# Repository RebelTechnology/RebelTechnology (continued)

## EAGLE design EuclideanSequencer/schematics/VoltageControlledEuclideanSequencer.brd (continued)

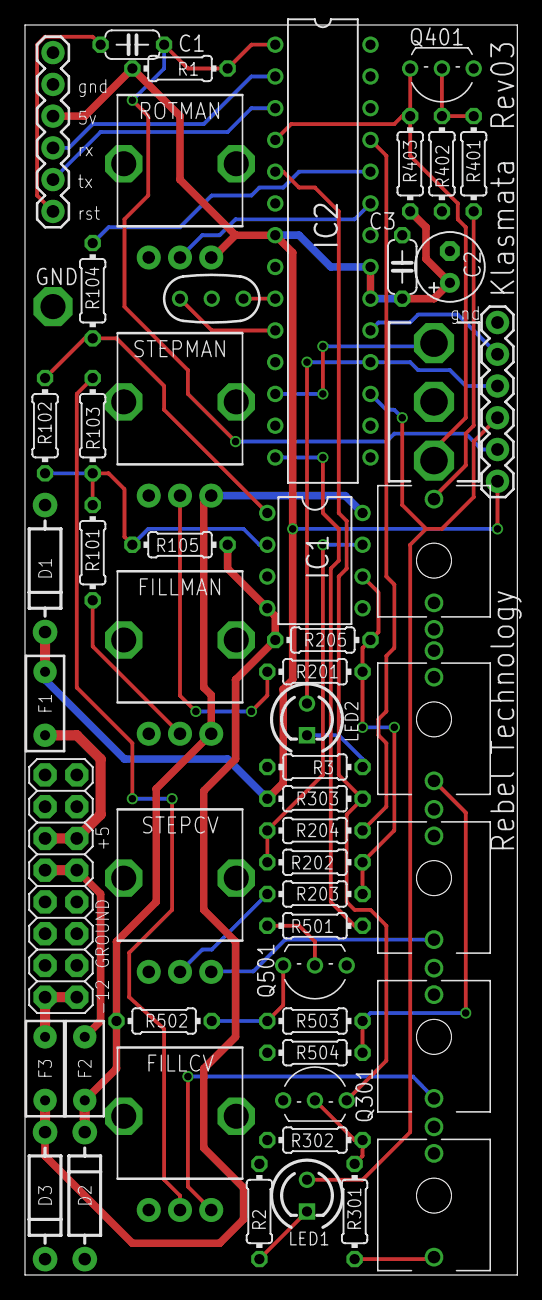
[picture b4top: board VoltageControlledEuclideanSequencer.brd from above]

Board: 2 copper layers, 39.4 x 100.0 mm, 57 parts (0 on the bottom side), 42 nets.

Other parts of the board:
U$1: RT-LOGO-REBEL-BL
U$3: RT-LOGO-TECH-BL

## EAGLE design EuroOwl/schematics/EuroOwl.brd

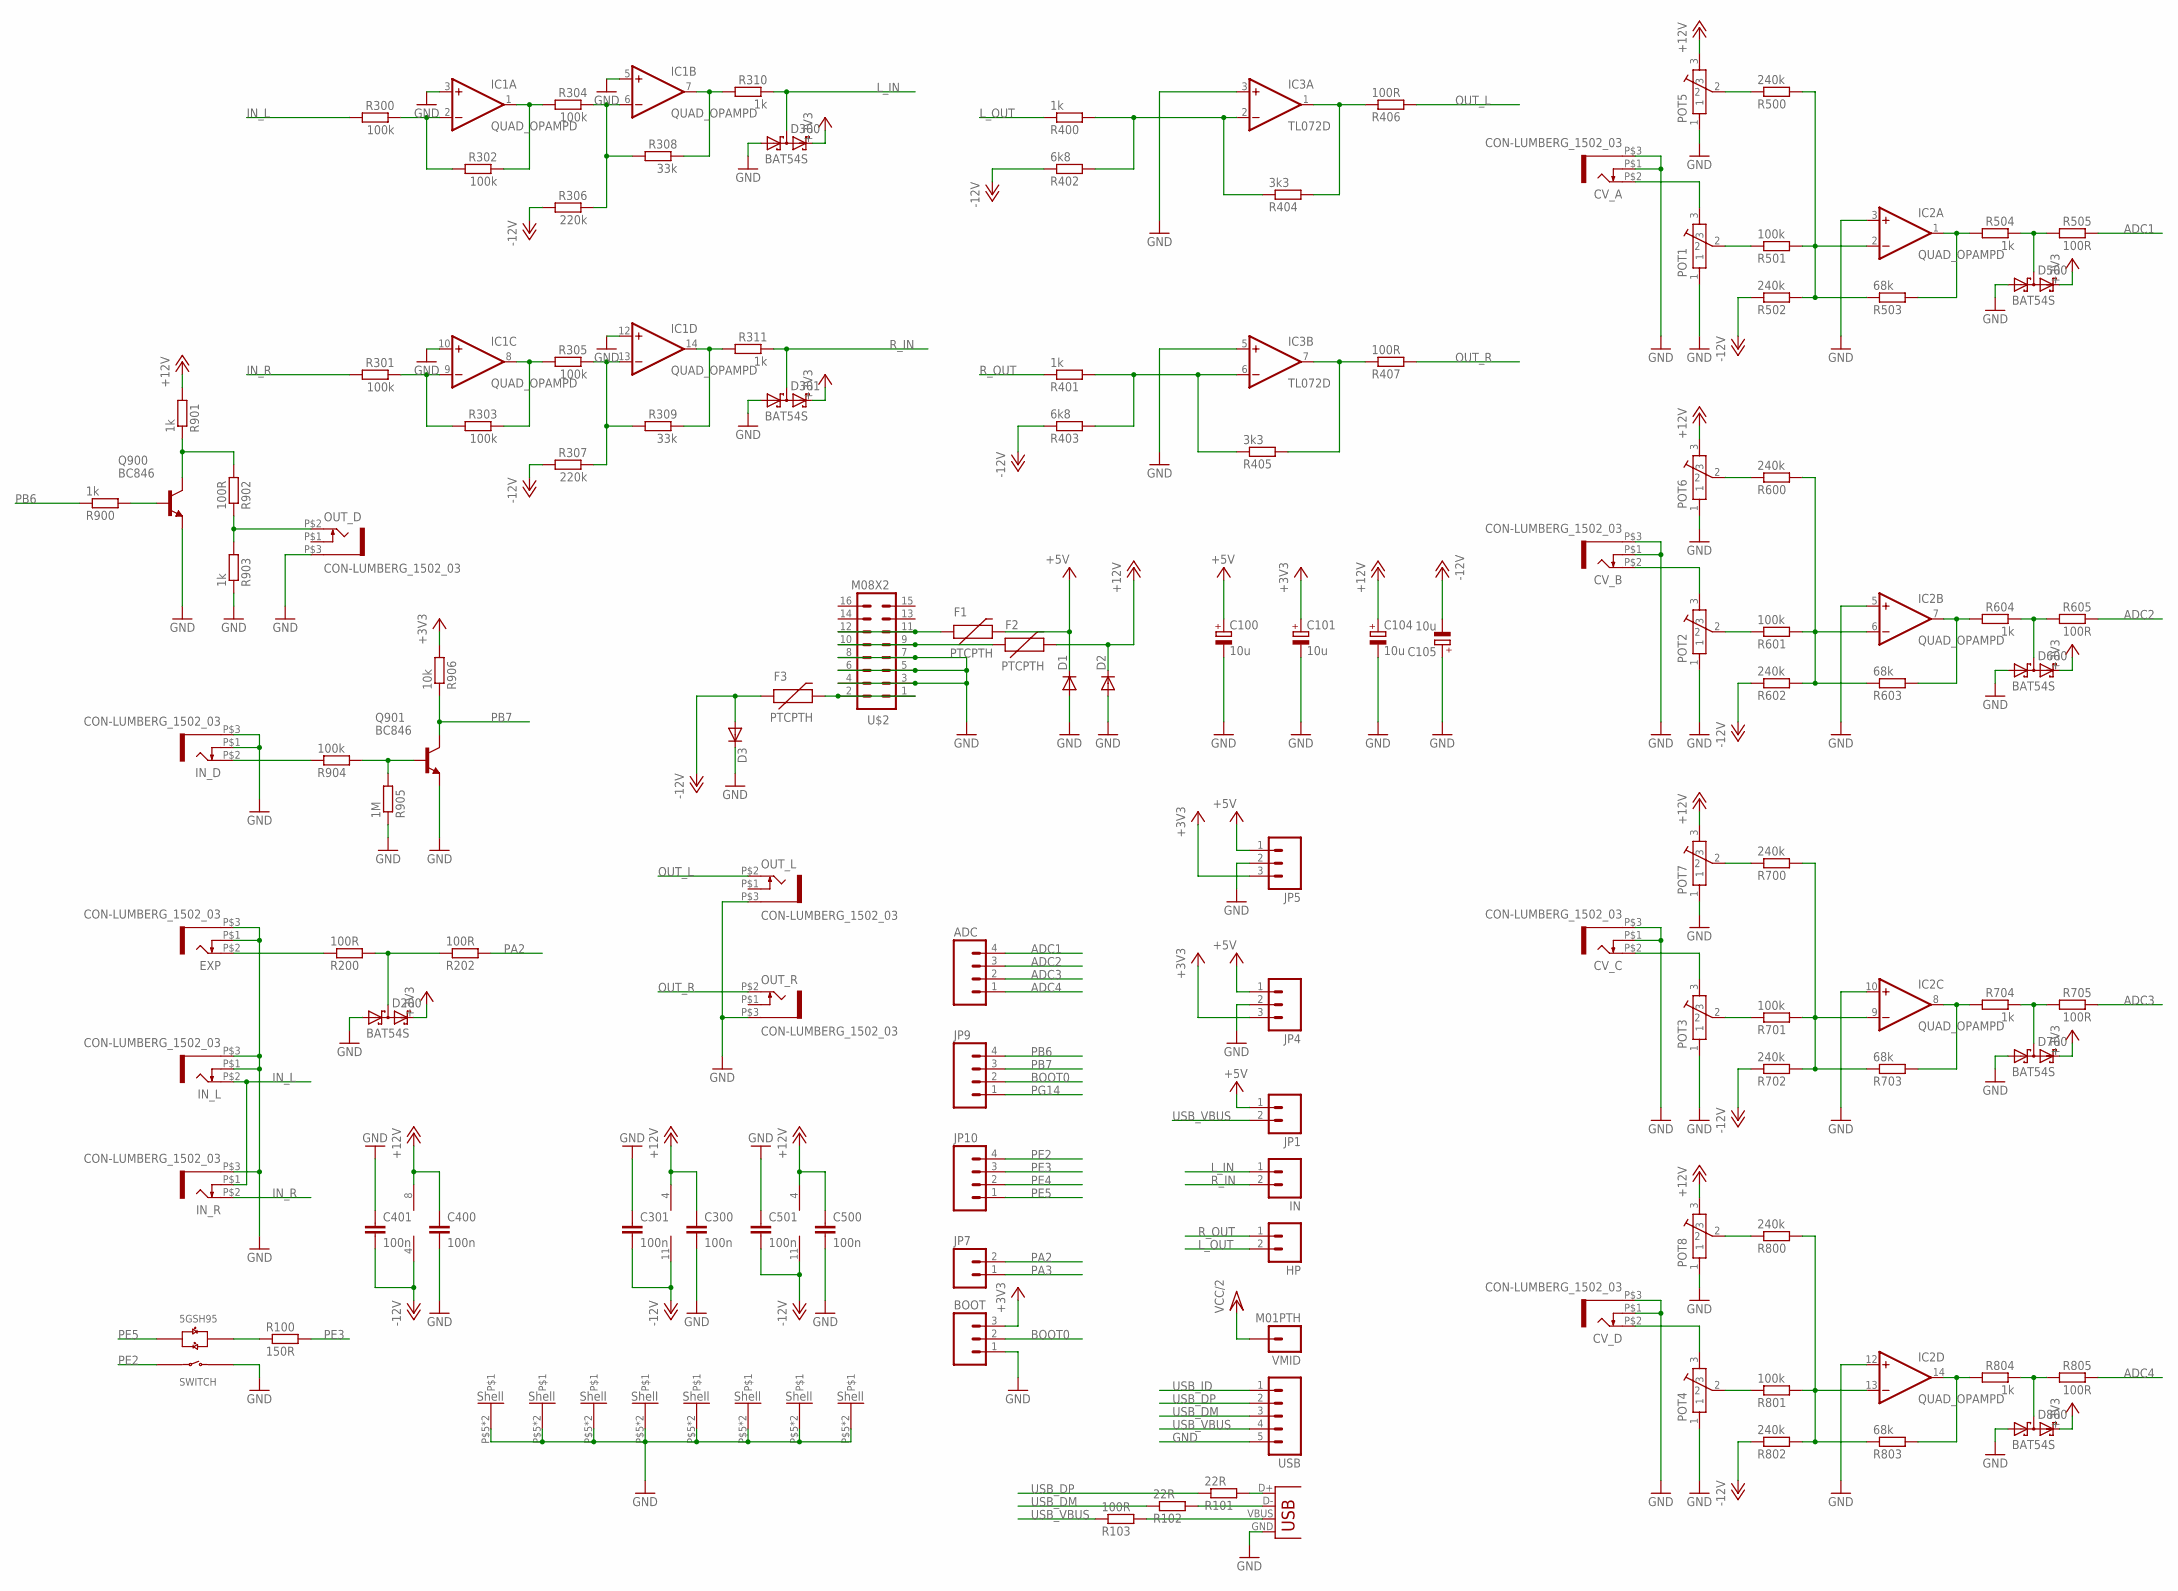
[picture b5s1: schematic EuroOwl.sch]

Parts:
ADC: M04PTH; 1X04
BOOT: M03PTH; 1X03
C100, C101, C104, C105: 10u; PANASONIC_A
C300, C301, C400, C401, C500, C501: 100n; C0603
CV_A: CON-LUMBERG_1502_03
CV_B: CON-LUMBERG_1502_03
CV_C: CON-LUMBERG_1502_03
CV_D: CON-LUMBERG_1502_03
D1, D2, D3: DIODE1N4001; DIODE-1N4001
D200, D300, D301, D500, D600, D700, D800: BAT54S; SOT23
EXP: CON-LUMBERG_1502_03
F1, F2, F3: PTCPTH; PTC
HP: M02PTH; 1X02
IC1, IC2: QUAD_OPAMPD; SO14
IC3: TL072D; SO08
IN: M02PTH; 1X02
IN_D: CON-LUMBERG_1502_03
IN_L: CON-LUMBERG_1502_03
IN_R: CON-LUMBERG_1502_03
JP1, JP7: M02PTH; 1X02
JP4, JP5: M03PTH; 1X03
JP9, JP10: M04PTH; 1X04
OUT_D: CON-LUMBERG_1502_03
OUT_L: CON-LUMBERG_1502_03
OUT_R: CON-LUMBERG_1502_03
POT1, POT2, POT3, POT4, POT5, POT6, POT7, POT8: POT-ALPS-RK09L1140
Q900, Q901: BC846; SOT23
R100: 150R; 0603
R101, R102: 22R; 0603
R103, R200, R202, R406, R407, R505, R605, R705, R805, R902: 100R; 0603
R300, R301, R302, R303, R304, R305, R501, R601, R701, R801, R904: 100k; 0603
R306, R307: 220k; 0603
R308, R309: 33k; 0603
R310, R311, R400, R401, R504, R604, R704, R804, R900, R901, R903: 1k; 0603
R402, R403: 6k8; 0603
R404, R405: 3k3; 0603
R500, R502, R600, R602, R700, R702, R800, R802: 240k; 0603
R503, R603, R703, R803: 68k; 0603
R905: 1M; 0603
R906: 10k; 0603
U$1: 5GTH9
U$2: M08X2; 2X8
USB: M05PTH; 1X05
VMID: M01PTH; 1X01
X1: USBPTH-VERTICAL; USB-B-PTH-VERTICAL

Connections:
+3V3: BOOT.3, C101.+, D200.2 (C2), D300.2 (C2), D301.2 (C2), D500.2 (C2), D600.2 (C2), D700.2 (C2), D800.2 (C2), JP4.3, JP5.3, R906.2
+5V: C100.+, D1.C, F1.P$2 (2), JP1.1, JP4.1, JP5.1
+12V: C104.+, C300.1, C400.1, C500.1, D2.C, F2.P$2 (2), IC1.4 (V+), IC2.4 (V+), IC3.8 (V+), POT5.3, POT6.3, POT7.3, POT8.3, R901.2
-12V: C105.-, C301.2, C401.2, C501.2, D3.A, F3.P$1 (1), IC1.11 (V-), IC2.11 (V-), IC3.4 (V-), R306.2, R307.2, R402.1, R403.1, R502.1, R602.1, R702.1, R802.1
ADC1: ADC.4, R505.1
ADC2: ADC.3, R605.1
ADC3: ADC.2, R705.1
ADC4: ADC.1, R805.1
BOOT0: BOOT.2, JP9.2
GND: BOOT.1, C100.-, C101.-, C104.-, C105.+, C300.2, C301.1, C400.2, C401.1, C500.2, C501.1, CV_A.P$1 (4), CV_A.P$3 (5), CV_B.P$1 (4), CV_B.P$3 (5), CV_C.P$1 (4), CV_C.P$3 (5), CV_D.P$1 (4), CV_D.P$3 (5), D1.A, D2.A, D3.C, D200.1 (A1), D300.1 (A1), D301.1 (A1), D500.1 (A1), D600.1 (A1), D700.1 (A1), D800.1 (A1), EXP.P$1 (4), EXP.P$3 (5), IC1.3 (+IN), IC1.5 (+IN), IC1.10 (+IN), IC1.12 (+IN), IC2.3 (+IN), IC2.5 (+IN), IC2.10 (+IN), IC2.12 (+IN), IC3.3 (+IN), IC3.5 (+IN), IN_D.P$1 (4), IN_D.P$3 (5), IN_L.P$1 (4), IN_L.P$3 (5), IN_R.P$3 (5), JP4.2, JP5.2, OUT_D.P$3 (5), OUT_L.P$3 (5), OUT_R.P$3 (5), POT1.1, POT1.P$5, POT1.P$6, POT2.1, POT2.P$5, POT2.P$6, POT3.1, POT3.P$5, POT3.P$6, POT4.1, POT4.P$5, POT4.P$6, POT5.1, POT5.P$5, POT5.P$6, POT6.1, POT6.P$5, POT6.P$6, POT7.1, POT7.P$5, POT7.P$6, POT8.1, POT8.P$5, POT8.P$6, Q900.2 (E), Q901.2 (E), R903.1, R905.1, U$1.1 (SWITCH_B), U$2.3, U$2.4, U$2.5, U$2.6, U$2.7, U$2.8, USB.5, X1.GND
IN_L: IN_L.P$2 (3), IN_R.P$1 (4), R300.2
IN_R: IN_R.P$2 (3), R301.2
L_IN: D300.3 (C1A2), IN.1, R310.1
L_OUT: HP.2, R400.1
unnamed: IC1.1 (OUT), R302.1, R304.2
unnamed: CV_A.P$2 (3), POT1.3
unnamed: POT1.2, R501.1
unnamed: IC1.8 (OUT), R303.1, R305.2
unnamed: IC1.9 (-IN), R301.1, R303.2
unnamed: F3.P$2 (2), U$2.1, U$2.2
unnamed: IC1.13 (-IN), R305.1, R307.1, R309.2
unnamed: IC1.2 (-IN), R300.1, R302.2
unnamed: R100.1, U$1.+3 (LED_R+)
unnamed: D200.3 (C1A2), R200.2, R202.1
unnamed: IC2.2 (-IN), R500.2, R501.2, R502.2, R503.1
unnamed: POT5.2, R500.1
unnamed: D500.3 (C1A2), R504.1, R505.2
unnamed: IC2.1 (OUT), R503.2, R504.2
unnamed: CV_B.P$2 (3), POT2.3
unnamed: POT2.2, R601.1
unnamed: IC2.6 (-IN), R600.2, R601.2, R602.2, R603.1
unnamed: POT6.2, R600.1
unnamed: IC2.7 (OUT), R603.2, R604.2
unnamed: D600.3 (C1A2), R604.1, R605.2
unnamed: CV_C.P$2 (3), POT3.3
unnamed: POT3.2, R701.1
unnamed: IC2.9 (-IN), R700.2, R701.2, R702.2, R703.1
unnamed: POT7.2, R700.1
unnamed: IC2.8 (OUT), R703.2, R704.2
unnamed: D700.3 (C1A2), R704.1, R705.2
unnamed: CV_D.P$2 (3), POT4.3
unnamed: POT4.2, R801.1
unnamed: IC1.6 (-IN), R304.1, R306.1, R308.2
unnamed: IC2.13 (-IN), R800.2, R801.2, R802.2, R803.1
unnamed: POT8.2, R800.1
unnamed: IC2.14 (OUT), R803.2, R804.2
unnamed: D800.3 (C1A2), R804.1, R805.2
unnamed: Q901.1 (B), R904.2, R905.2
unnamed: EXP.P$2 (3), R200.1
unnamed: IC3.1 (OUT), R404.2, R406.1
unnamed: IC3.7 (OUT), R405.2, R407.1
unnamed: IC3.2 (-IN), R400.2, R402.2, R404.1
unnamed: IC3.6 (-IN), R401.2, R403.2, R405.1
unnamed: F1.P$1 (1), U$2.11, U$2.12
unnamed: F2.P$1 (1), U$2.9, U$2.10
unnamed: IN_D.P$2 (3), R904.1
unnamed: Q900.3 (C), R901.1, R902.2
unnamed: OUT_D.P$2 (3), R902.1, R903.2
unnamed: Q900.1 (B), R900.2
unnamed: R101.2, X1.D+
unnamed: R102.2, X1.D-
unnamed: IC1.14 (OUT), R309.1, R311.2
unnamed: R103.2, X1.VBUS
unnamed: IC1.7 (OUT), R308.1, R310.2
OUT_L: OUT_L.P$2 (3), R406.2
OUT_R: OUT_R.P$2 (3), R407.2
PA2: JP7.2, R202.2
PA3: JP7.1
PB6: JP9.4, R900.1
PB7: JP9.3, Q901.3 (C), R906.1
PE2: JP10.4, U$1.4 (SWITCH_A)
PE3: JP10.3, R100.2
PE4: JP10.2
PE5: JP10.1, U$1.-2 (LED_G+)
PG14: JP9.1
R_IN: D301.3 (C1A2), IN.2, R311.1
R_OUT: HP.1, R401.1
USB_DM: R102.1, USB.3
USB_DP: R101.1, USB.2
USB_ID: USB.1
USB_VBUS: JP1.2, R103.1, USB.4
VCC/2: VMID.1

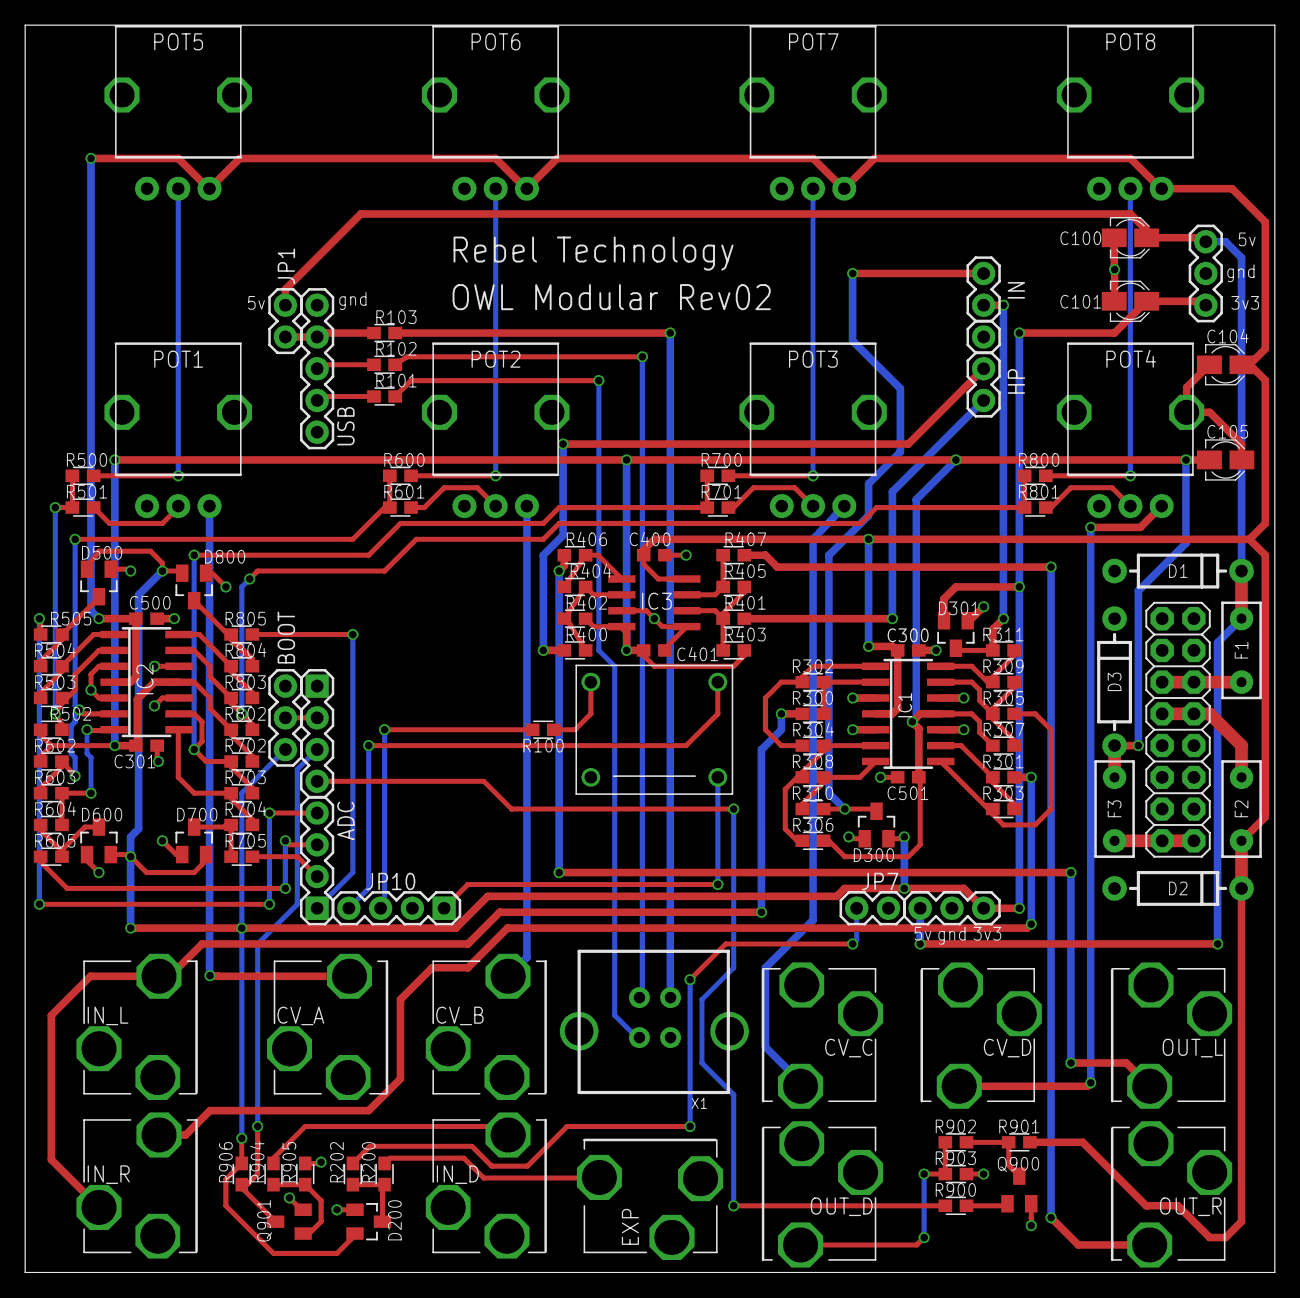
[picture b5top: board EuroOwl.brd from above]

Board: 2 copper layers, 100.0 x 99.8 mm, 119 parts (0 on the bottom side), 77 nets.

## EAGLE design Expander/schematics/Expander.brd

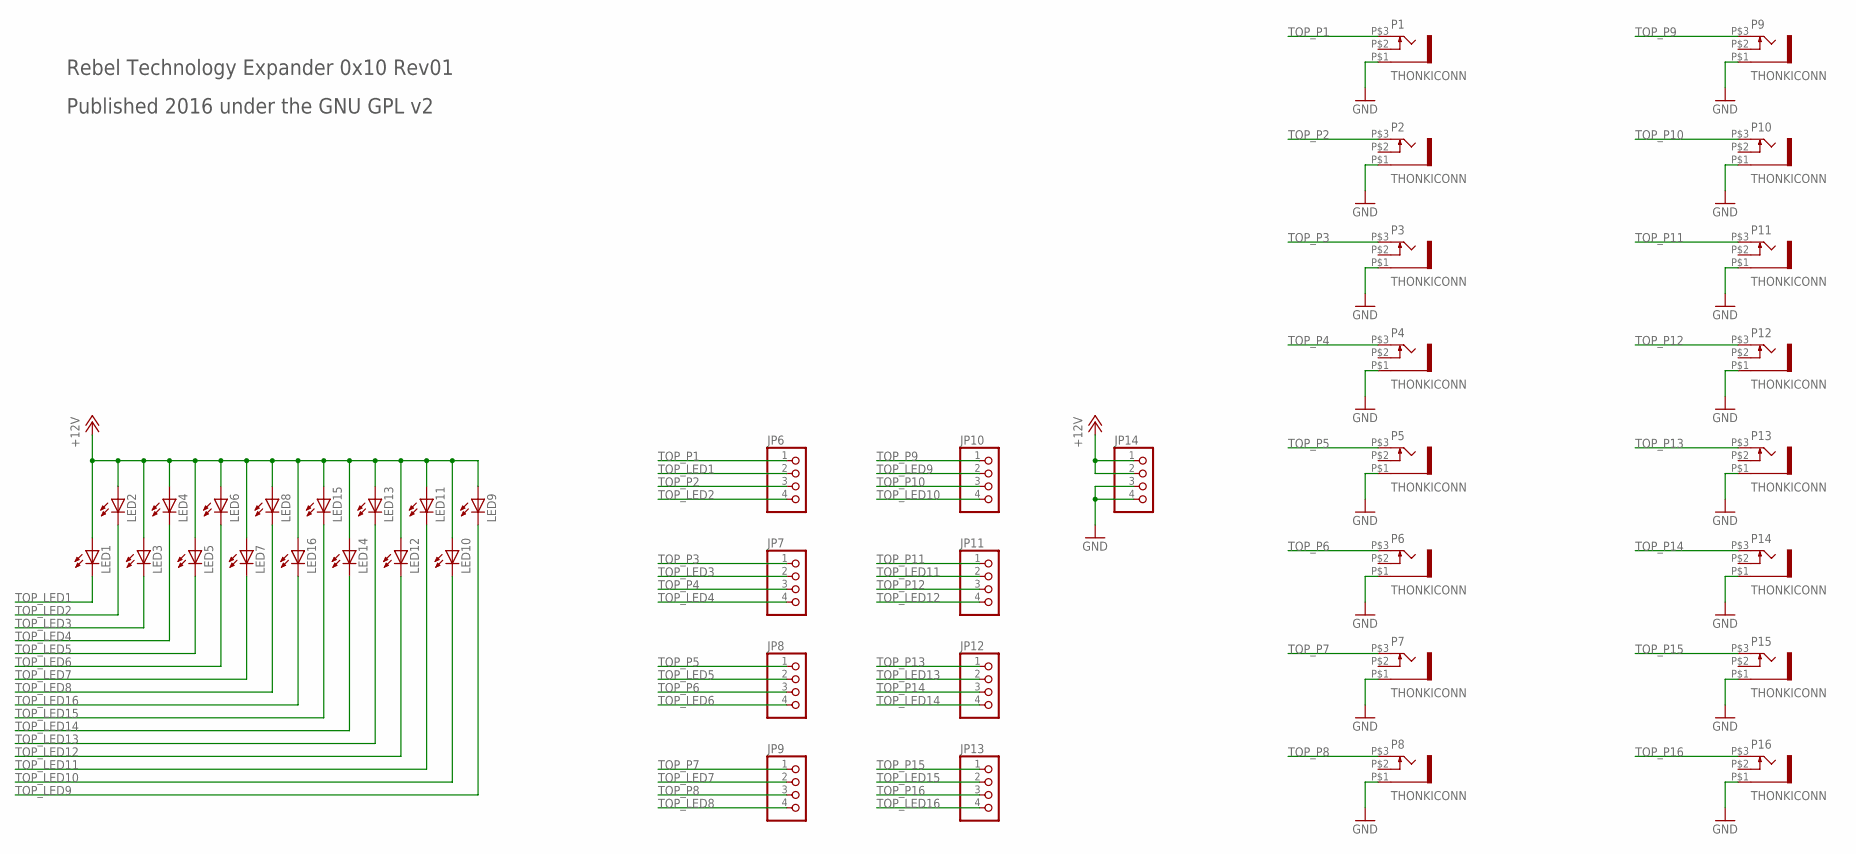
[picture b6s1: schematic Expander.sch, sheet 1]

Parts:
JP6, JP7, JP8, JP9, JP10, JP11, JP12, JP13, JP14: PINHD-1X4; 1X04
LED1, LED2, LED3, LED4, LED5, LED6, LED7, LED8, LED9, LED10, LED11, LED12, LED13, LED14, LED15, LED16: LED3MM
P1, P2, P3, P4, P5, P6, P7, P8, P9, P10, P11, P12, P13, P14, P15, P16: THONKICONN

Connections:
TOP_+12V: JP14.1, JP14.2, LED1.A, LED2.A, LED3.A, LED4.A, LED5.A, LED6.A, LED7.A, LED8.A, LED9.A, LED10.A, LED11.A, LED12.A, LED13.A, LED14.A, LED15.A, LED16.A
TOP_GND: JP14.3, JP14.4, P1.P$1 (5), P2.P$1 (5), P3.P$1 (5), P4.P$1 (5), P5.P$1 (5), P6.P$1 (5), P7.P$1 (5), P8.P$1 (5), P9.P$1 (5), P10.P$1 (5), P11.P$1 (5), P12.P$1 (5), P13.P$1 (5), P14.P$1 (5), P15.P$1 (5), P16.P$1 (5)
TOP_LED1: JP6.2, LED1.K (C)
TOP_LED2: JP6.4, LED2.K (C)
TOP_LED3: JP7.2, LED3.K (C)
TOP_LED4: JP7.4, LED4.K (C)
TOP_LED5: JP8.2, LED5.K (C)
TOP_LED6: JP8.4, LED6.K (C)
TOP_LED7: JP9.2, LED7.K (C)
TOP_LED8: JP9.4, LED8.K (C)
TOP_LED9: JP10.2, LED9.K (C)
TOP_LED10: JP10.4, LED10.K (C)
TOP_LED11: JP11.2, LED11.K (C)
TOP_LED12: JP11.4, LED12.K (C)
TOP_LED13: JP12.2, LED13.K (C)
TOP_LED14: JP12.4, LED14.K (C)
TOP_LED15: JP13.2, LED15.K (C)
TOP_LED16: JP13.4, LED16.K (C)
TOP_P1: JP6.1, P1.P$3 (3)
TOP_P2: JP6.3, P2.P$3 (3)
TOP_P3: JP7.1, P3.P$3 (3)
TOP_P4: JP7.3, P4.P$3 (3)
TOP_P5: JP8.1, P5.P$3 (3)
TOP_P6: JP8.3, P6.P$3 (3)
TOP_P7: JP9.1, P7.P$3 (3)
TOP_P8: JP9.3, P8.P$3 (3)
TOP_P9: JP10.1, P9.P$3 (3)
TOP_P10: JP10.3, P10.P$3 (3)
TOP_P11: JP11.1, P11.P$3 (3)
TOP_P12: JP11.3, P12.P$3 (3)
TOP_P13: JP12.1, P13.P$3 (3)
TOP_P14: JP12.3, P14.P$3 (3)
TOP_P15: JP13.1, P15.P$3 (3)
TOP_P16: JP13.3, P16.P$3 (3)

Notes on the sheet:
Rebel Technology Expander 0x10 Rev01
Published 2016 under the GNU GPL v2

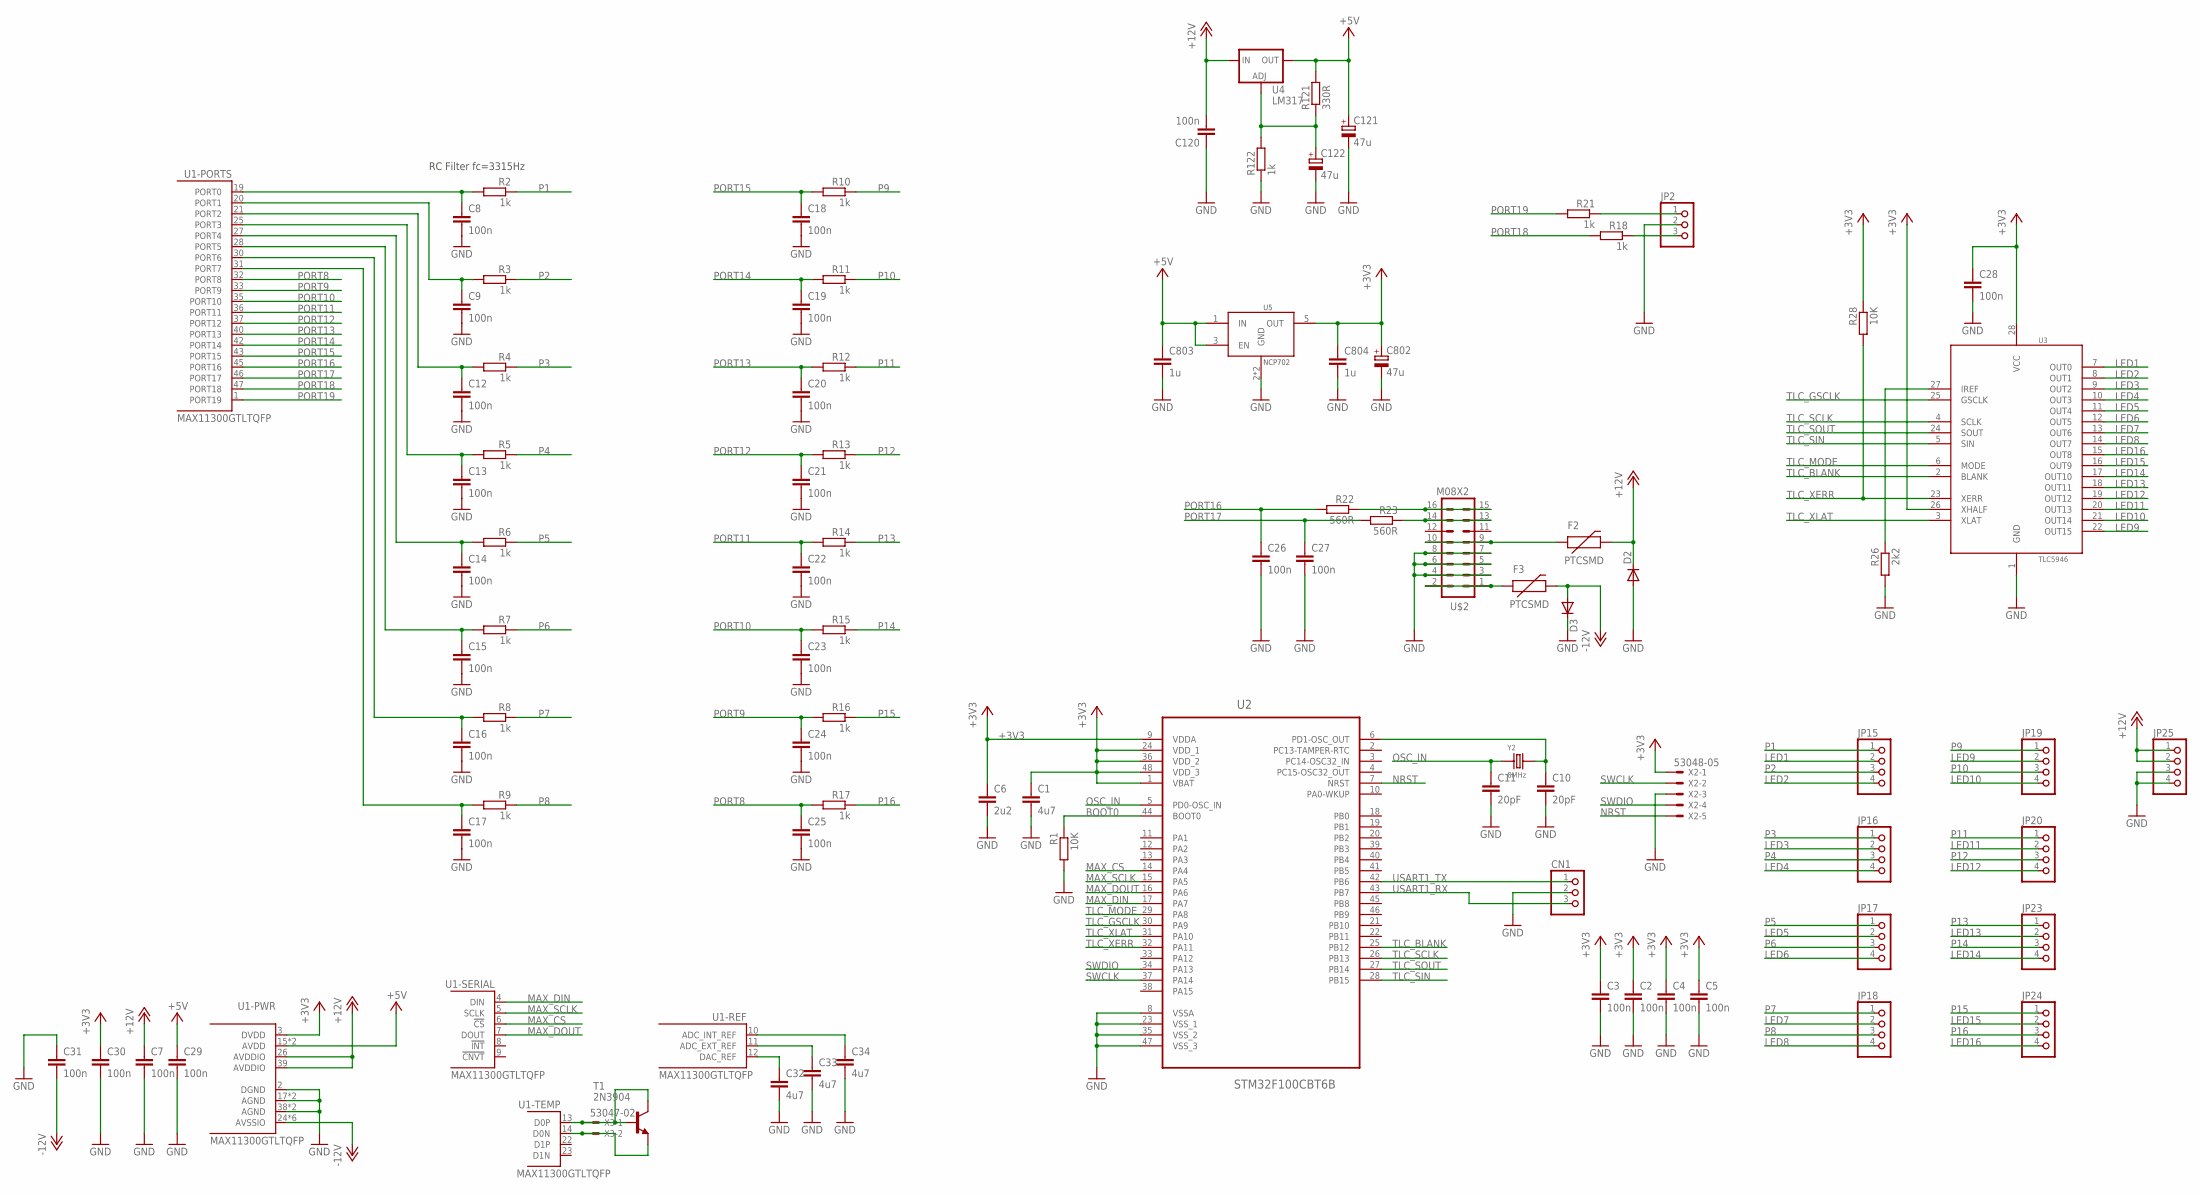
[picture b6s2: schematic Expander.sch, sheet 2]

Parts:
C1, C32, C33, C34: 4u7; C0603
C2, C3, C4, C5, C7, C8, C9, C12, C13, C14, C15, C16, C17, C18, C19, C20, C21, C22, C23, C24, C25, C26, C27, C28, C29, C30, C31, C120: 100n; C0603
C6: 2u2; C0603
C10, C11: 20pF; C0603
C121, C122, C802: 47u; CPOL-5
C803, C804: 1u; C0603
CN1: CON-JST-1X03PH-TH; JST-B3B-PH-KL
D2, D3: DIODESMA; SMA-DIODE
F2, F3: PTCSMD; PTC-1206
JP2: PINHD-1X3; 1X03
JP15, JP16, JP17, JP18, JP19, JP20, JP23, JP24, JP25: PINHD-1X4; 1X04
R1, R28: 10K; 0603
R2, R3, R4, R5, R6, R7, R8, R9, R10, R11, R12, R13, R14, R15, R16, R17, R18, R21, R122: 1k; 0603
R22, R23: 560R; 0603
R26: 2k2; 0603
R121: 330R; 0603
T1: 2N3904; TO92
U1: MAX11300GTLTQFP; TQFP48
U2: STM32F100CBT6B; QFP50P900X900X160-48N
U3: TLC5946; TSSOP28
U4: LM317; SOT223
U5: NCP702; TSOP-5
U$2: M08X2; 2X8
X2: 53048-05
X3: 53047-02
Y2: 8MHz; X2-SMD-5.0X3.2X1.3MM

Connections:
+3V3: C1.1, C2.1, C3.1, C4.1, C5.1, C6.1, C28.1, C30.1, C802.+, C804.1, R28.1, U1.3 (DVDD), U2.1 (VBAT), U2.9 (VDDA), U2.24 (VDD_1), U2.36 (VDD_2), U2.48 (VDD_3), U3.26 (XHALF), U3.28 (VCC), U5.5 (OUT), X2.1
+5V: C29.1, C121.+, C803.1, R121.2, U1.15 (AVDD), U1.16 (AVDD), U4.2 (OUT), U4.4 (OUT), U5.1 (IN), U5.3 (EN)
+12V: C7.1, C120.2, D2.C, F2.2, JP25.1, JP25.2, U1.26 (AVDDIO), U1.39 (AVDDIO), U4.3 (IN)
-12V: C31.2, D3.A, F3.2, U1.24 (AVSSIO), U1.29 (AVSSIO), U1.34 (AVSSIO), U1.41 (AVSSIO), U1.44 (AVSSIO), U1.48 (AVSSIO)
BOOT0: R1.1, U2.44 (BOOT0)
D0N: T1.3 (E), U1.14 (D0N), X3.2
D0P: T1.1 (C), T1.2 (B), U1.13 (D0P), X3.1
GND: C1.2, C2.2, C3.2, C4.2, C5.2, C6.2, C7.2, C8.2, C9.2, C10.2, C11.2, C12.2, C13.2, C14.2, C15.2, C16.2, C17.2, C18.2, C19.2, C20.2, C21.2, C22.2, C23.2, C24.2, C25.2, C26.2, C27.2, C28.2, C29.2, C30.2, C31.1, C32.2, C33.2, C34.2, C120.1, C121.-, C122.-, C802.-, C803.2, C804.2, CN1.2, D2.A, D3.C, JP2.2, JP25.3, JP25.4, R1.2, R26.2, R122.1, U1.2 (DGND), U1.17 (AGND), U1.18 (AGND), U1.38 (AGND), U1.EP (AGND), U2.8 (VSSA), U2.23 (VSS_1), U2.35 (VSS_2), U2.47 (VSS_3), U3.1 (GND), U5.2 (GND), U5.4 (GND), U$2.3, U$2.4, U$2.5, U$2.6, U$2.7, U$2.8, X2.3
LED1: JP15.2, U3.7 (OUT0)
LED2: JP15.4, U3.8 (OUT1)
LED3: JP16.2, U3.9 (OUT2)
LED4: JP16.4, U3.10 (OUT3)
LED5: JP17.2, U3.11 (OUT4)
LED6: JP17.4, U3.12 (OUT5)
LED7: JP18.2, U3.13 (OUT6)
LED8: JP18.4, U3.14 (OUT7)
LED9: JP19.2, U3.22 (OUT15)
LED10: JP19.4, U3.21 (OUT14)
LED11: JP20.2, U3.20 (OUT13)
LED12: JP20.4, U3.19 (OUT12)
LED13: JP23.2, U3.18 (OUT11)
LED14: JP23.4, U3.17 (OUT10)
LED15: JP24.2, U3.16 (OUT9)
LED16: JP24.4, U3.15 (OUT8)
MAX_CS: U1.6 (!CS!), U2.14 (PA4)
MAX_DIN: U1.4 (DIN), U2.17 (PA7)
MAX_DOUT: U1.7 (DOUT), U2.16 (PA6)
MAX_SCLK: U1.5 (SCLK), U2.15 (PA5)
unnamed: C10.1, U2.6 (PD1-OSC_OUT), Y2.2
unnamed: C34.1, U1.10 (ADC_INT_REF)
unnamed: JP2.1, R21.1
unnamed: C33.1, U1.11 (ADC_EXT_REF)
unnamed: C32.1, U1.12 (DAC_REF)
unnamed: F3.1, U$2.1, U$2.2
unnamed: JP2.3, R18.1
unnamed: R22.1, U$2.15, U$2.16
unnamed: C122.+, R121.1, R122.2, U4.1 (ADJ)
unnamed: R23.1, U$2.13, U$2.14
unnamed: R26.1, U3.27 (IREF)
unnamed: F2.1, U$2.9, U$2.10
NRST: U2.7 (NRST), X2.5
OSC_IN: C11.1, U2.5 (PD0-OSC_IN), Y2.1
P1: JP15.1, R2.1
P2: JP15.3, R3.1
P3: JP16.1, R4.1
P4: JP16.3, R5.1
P5: JP17.1, R6.1
P6: JP17.3, R7.1
P7: JP18.1, R8.1
P8: JP18.3, R9.1
P9: JP19.1, R10.1
P10: JP19.3, R11.1
P11: JP20.1, R12.1
P12: JP20.3, R13.1
P13: JP23.1, R14.1
P14: JP23.3, R15.1
P15: JP24.1, R16.1
P16: JP24.3, R17.1
PORT0: C8.1, R2.2, U1.19 (PORT0)
PORT1: C9.1, R3.2, U1.20 (PORT1)
PORT2: C12.1, R4.2, U1.21 (PORT2)
PORT3: C13.1, R5.2, U1.25 (PORT3)
PORT4: C14.1, R6.2, U1.27 (PORT4)
PORT5: C15.1, R7.2, U1.28 (PORT5)
PORT6: C16.1, R8.2, U1.30 (PORT6)
PORT7: C17.1, R9.2, U1.31 (PORT7)
PORT8: C25.1, R17.2, U1.32 (PORT8)
PORT9: C24.1, R16.2, U1.33 (PORT9)
PORT10: C23.1, R15.2, U1.35 (PORT10)
PORT11: C22.1, R14.2, U1.36 (PORT11)
PORT12: C21.1, R13.2, U1.37 (PORT12)
PORT13: C20.1, R12.2, U1.40 (PORT13)
PORT14: C19.1, R11.2, U1.42 (PORT14)
PORT15: C18.1, R10.2, U1.43 (PORT15)
PORT16: C26.1, R22.2, U1.45 (PORT16)
PORT17: C27.1, R23.2, U1.46 (PORT17)
PORT18: R18.2, U1.47 (PORT18)
PORT19: R21.2, U1.1 (PORT19)
SWCLK: U2.37 (PA14), X2.2
SWDIO: U2.34 (PA13), X2.4
TLC_BLANK: U2.25 (PB12), U3.2 (BLANK)
TLC_GSCLK: U2.30 (PA9), U3.25 (GSCLK)
TLC_MODE: U2.29 (PA8), U3.6 (MODE)
TLC_SCLK: U2.26 (PB13), U3.4 (SCLK)
TLC_SIN: U2.28 (PB15), U3.5 (SIN)
TLC_SOUT: U2.27 (PB14), U3.24 (SOUT)
TLC_XERR: R28.2, U2.32 (PA11), U3.23 (XERR)
TLC_XLAT: U2.31 (PA10), U3.3 (XLAT)
USART1_RX: CN1.3, U2.43 (PB7)
USART1_TX: CN1.1, U2.42 (PB6)

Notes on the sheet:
RC Filter fc=3315Hz

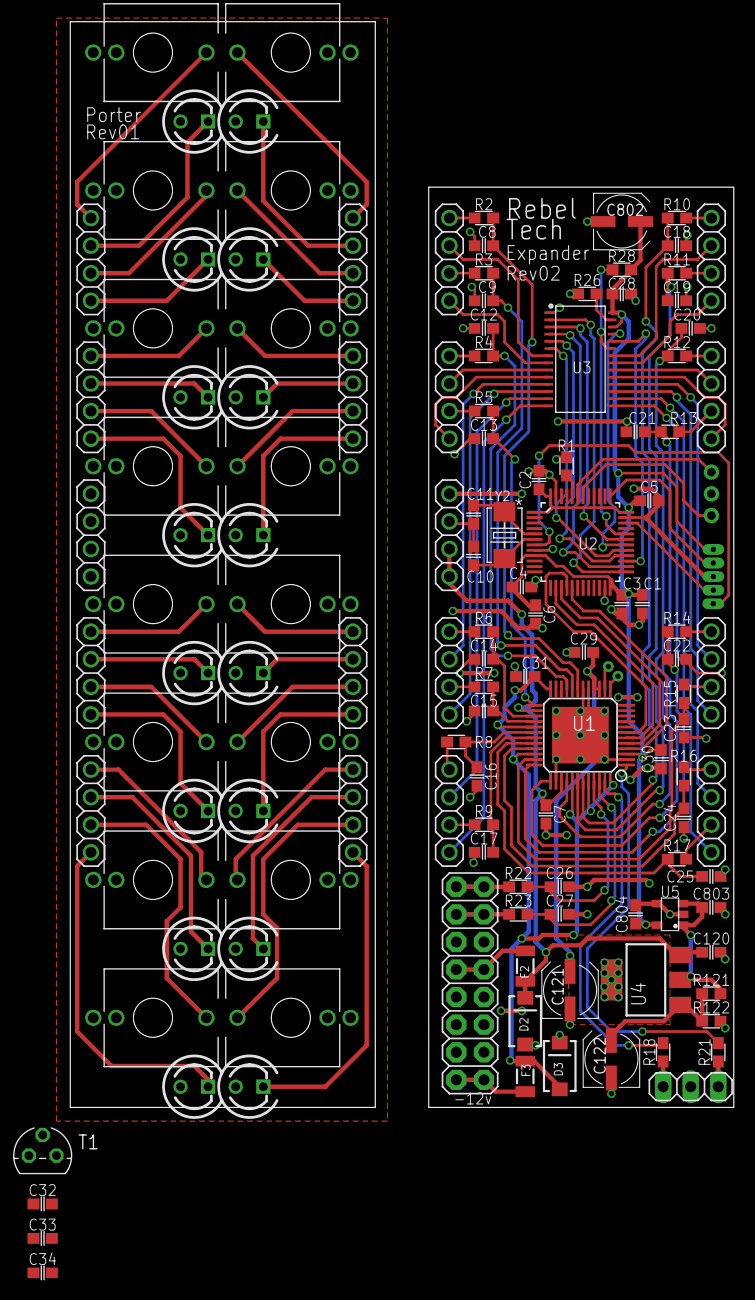
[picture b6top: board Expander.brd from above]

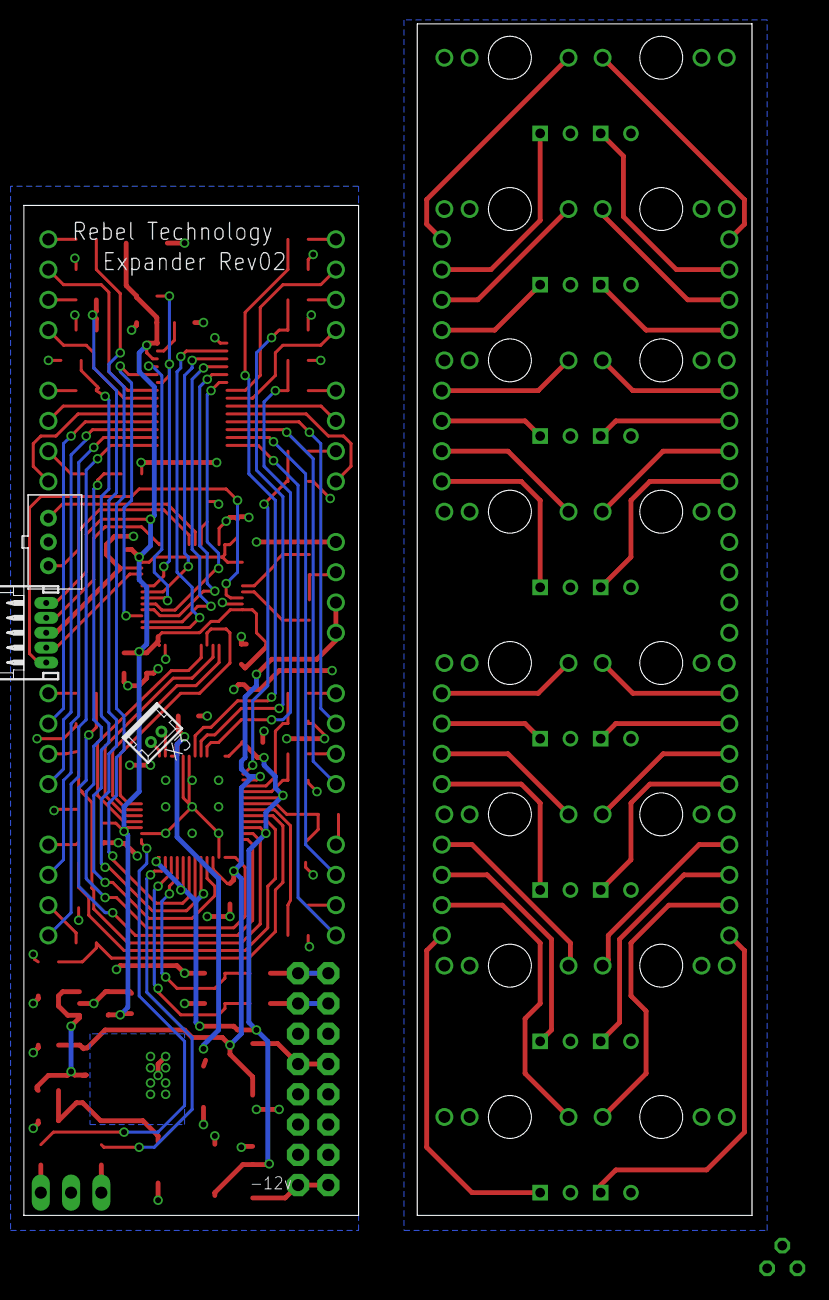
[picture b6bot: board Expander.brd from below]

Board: 2 copper layers, 61.1 x 100.0 mm, 131 parts (3 on the bottom side), 124 nets.
